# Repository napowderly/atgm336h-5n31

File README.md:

## **ATGM336H-5N31 GPS Module**

A super cheap GPS module with external UFL antenna.

## Features

- **Dimensions:** 13mm x 16mm
- **Supply Voltage:** 2.7V - 3.6V
- **Average Power Consumption:** <25mA (@3.3V)
- **Communication:** Compatible with BeiDou Navigation Satellite Systems (BDS) and Global Navigation Satellite Systems (GNSS)
- **Tracking Channels:** 32
- **Capabilities:** Reads up to six satellite navigation systems and implements joint positioning, navigation, and timing.
- **Positioning Precision:** 2.5m
- **Time to First Fix:** ~32s
- **Update Rate:** 1Hz-10Hz
- **Serial Baudrate:** 9600 (default)
- **Operational Temperature Range:** -40℃ to +85℃

## Contact
For further inquiries or support, please contact me at narayan@atopile.io.

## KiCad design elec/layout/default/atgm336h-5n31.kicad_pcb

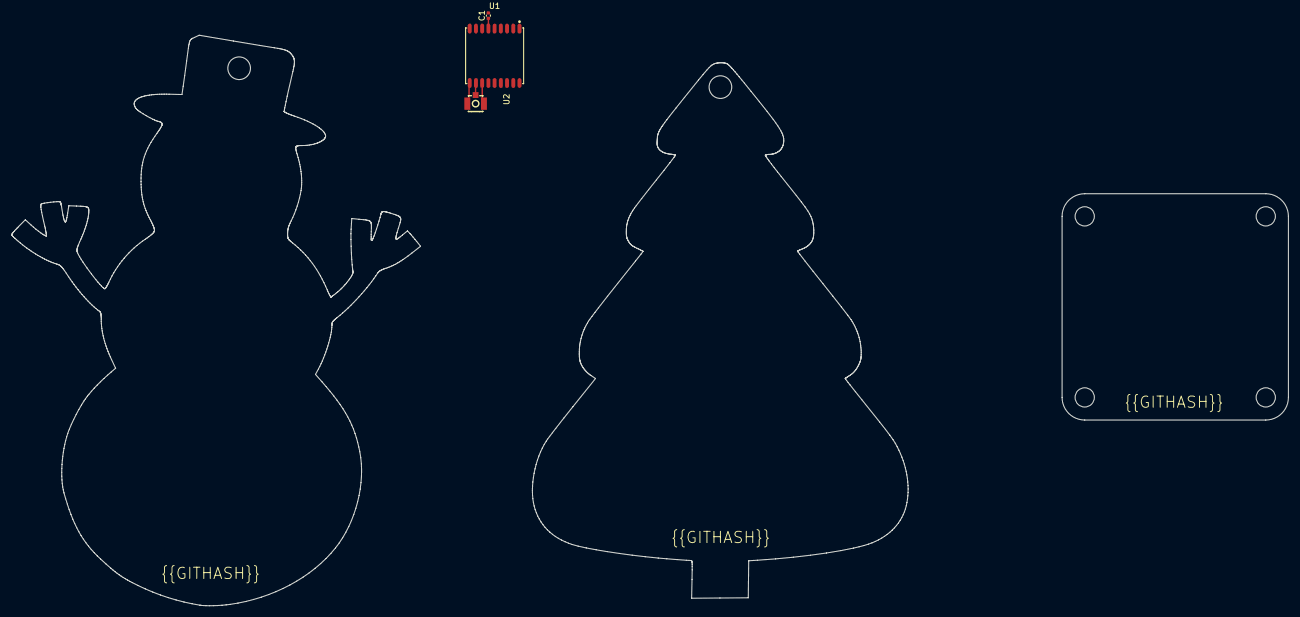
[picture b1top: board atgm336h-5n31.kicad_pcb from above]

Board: 2 copper layers, 3 parts (0 on the bottom side), 3 nets.

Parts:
C1: Multilayer Ceramic Capacitors MLCC - SMD/SMT 1uF 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; C0402
U1: GPSM-SMD_ATGM336H-TR
U2: IPEX-SMD_BWIPX-1-001E

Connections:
gnd: C1.2, U1.1, U1.10, U1.12, U2.2, U2.3
rf_in: U1.11, U2.1
vcc: C1.1, U1.6

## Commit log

2024-02-13 Configure project
2024-02-14 connect up vcc pins
2024-02-15 Update readme with image and features
